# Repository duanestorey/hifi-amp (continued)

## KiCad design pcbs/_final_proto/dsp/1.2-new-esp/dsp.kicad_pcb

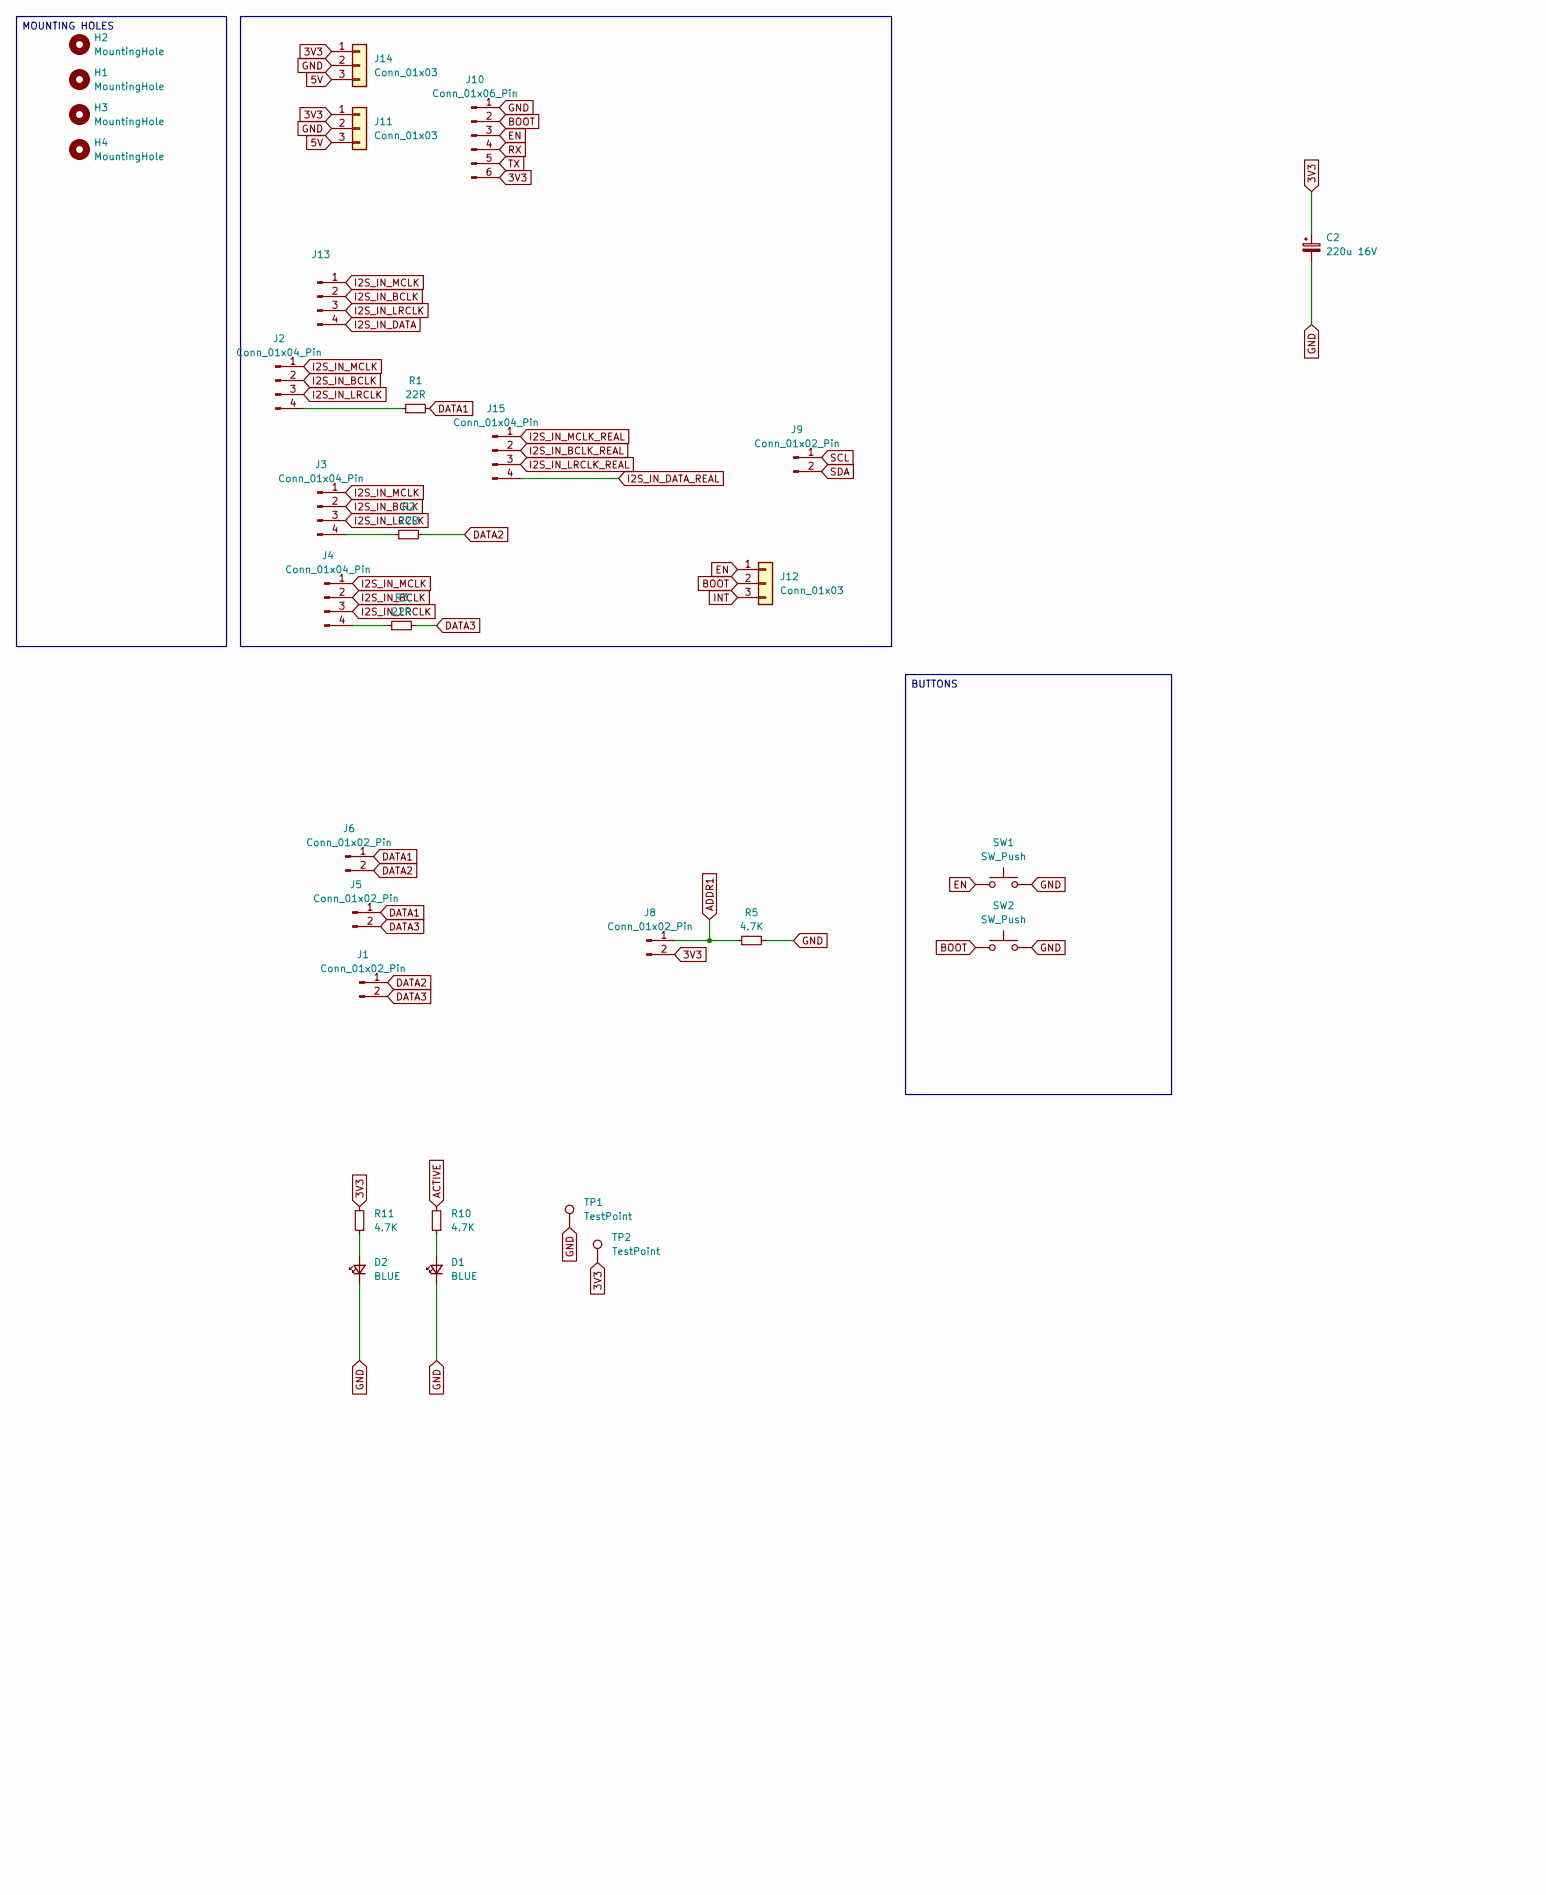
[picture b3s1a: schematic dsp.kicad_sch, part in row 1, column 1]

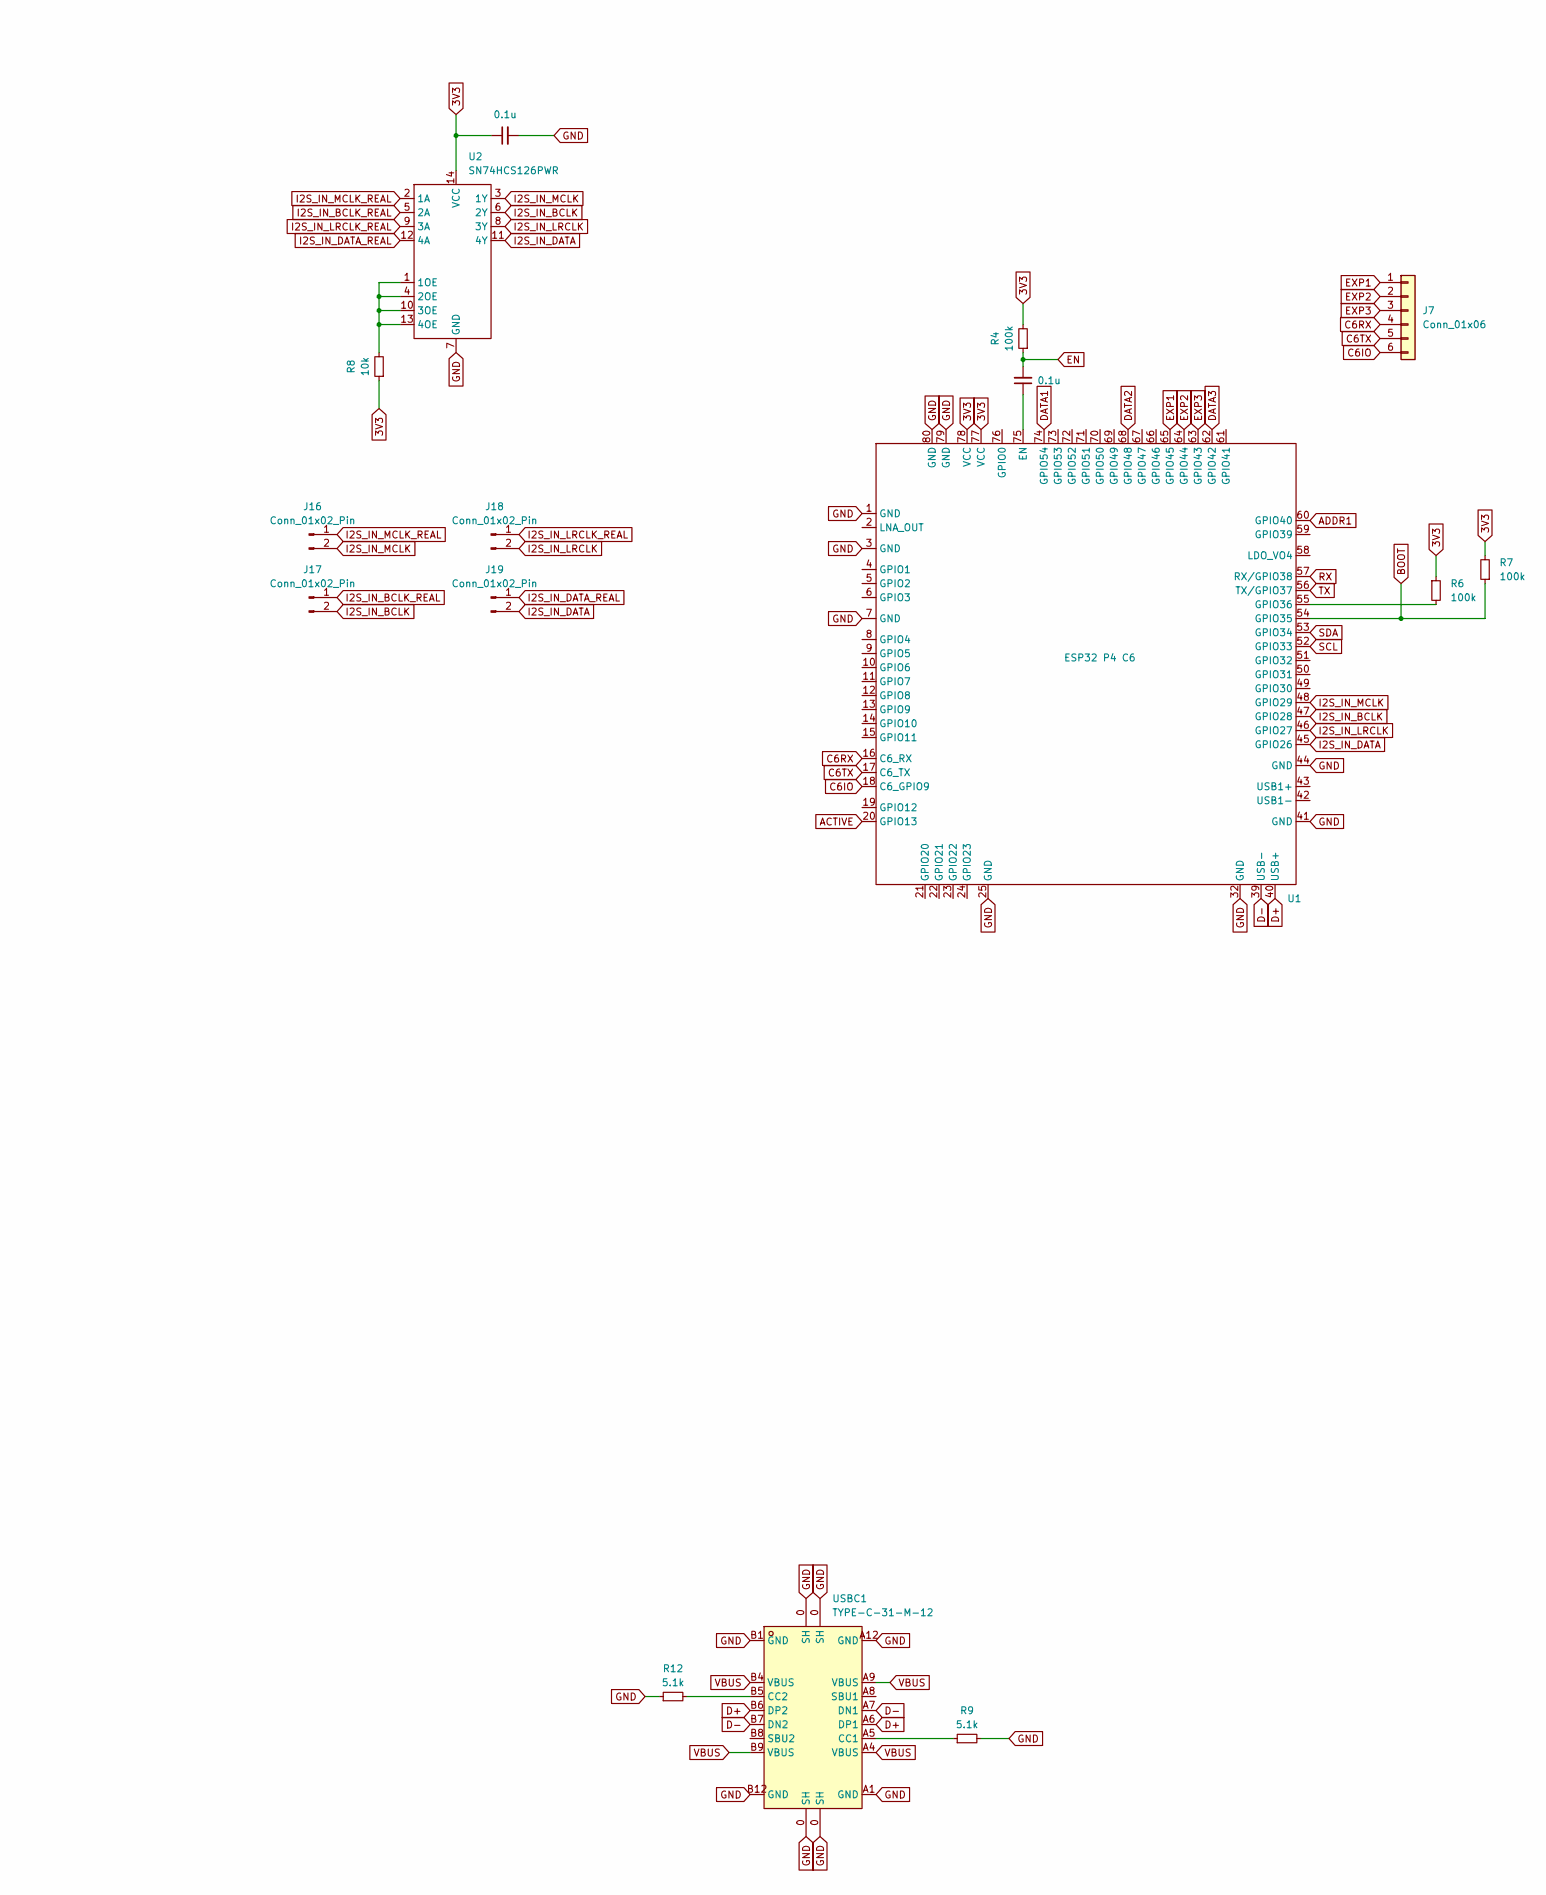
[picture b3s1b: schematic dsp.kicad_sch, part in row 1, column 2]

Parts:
C1, C3: 0.1u; C_0805_2012Metric_Pad1.18x1.45mm_HandSolder
C2: 220u 16V; CP_Elec_6.3x7.7
D1, D2: BLUE; LED_0805_2012Metric_Pad_HandSolder_Duane
H1, H2, H3, H4: MountingHole; MountingHole_3.2mm_M3_DIN965_Pad_TopOnly
J1, J5, J6, J8, J16, J17, J18, J19: Conn_01x02_Pin; PinHeader_1x02_P2.54mm_Vertical
J2, J3, J4, J15: Conn_01x04_Pin; JST_PH_B4B-PH-K_1x04_P2.00mm_Vertical
J7: Conn_01x06; PinHeader_1x06_P2.54mm_Vertical
J9: Conn_01x02_Pin; JST_PH_B2B-PH-K_1x02_P2.00mm_Vertical
J10: Conn_01x06_Pin; PinHeader_1x06_P2.54mm_Vertical
J11, J12, J14: Conn_01x03; JST_PH_B3B-PH-K_1x03_P2.00mm_Vertical
J13: Conn_01x04_Pin; PinHeader_1x04_P2.54mm_Vertical
R1, R2, R3: 22R; R_0805_2012Metric_Pad1.20x1.40mm_HandSolder_Duane; LCSC C23162
R4, R6, R7: 100k; R_0805_2012Metric_Pad1.20x1.40mm_HandSolder_Duane; Mouser 603-RT0805FRE0722RL
R5, R10, R11: 4.7K; R_0805_2012Metric_Pad1.20x1.40mm_HandSolder_Duane; LCSC C23162
R8: 10k; R_0805_2012Metric_Pad1.20x1.40mm_HandSolder_Duane; Mouser 603-RT0805FRE0722RL
R9, R12: 5.1k; R_0805_2012Metric_Pad1.20x1.40mm_HandSolder_Duane; Mouser 603-RT0805FRE0722RL
SW1, SW2: SW_Push; Button Aliexpress 4x4
TP1, TP2: TestPoint; TestPoint_THTPad_1.5x1.5mm_Drill0.7mm
U1: ESP32 P4 C6; ESP32 P4 C6 Module SoC Duane
U2: SN74HCS126PWR; TSSOP-14_4.4x5mm_P0.65mm; Mouser SN74HCS126PWR
USBC1: TYPE-C-31-M-12; USB-C - Duane; LCSC Part C165948

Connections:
3V3: C2.1, C3.1, J8.2, J10.6, J11.1, J14.1, R4.2, R6.1, R7.2, R8.1, R11.2, TP2.1, U1.77 (VCC), U1.78 (VCC), U2.14 (VCC)
5V: J11.3, J14.3
ACTIVE: R10.2, U1.20 (GPIO13)
ADDR1: J8.1, R5.1, U1.60 (GPIO40)
BOOT: J10.2, J12.2, R7.1, SW2.1, U1.54 (GPIO35)
C6IO: J7.6, U1.18 (C6_GPIO9)
C6RX: J7.4, U1.16 (C6_RX)
C6TX: J7.5, U1.17 (C6_TX)
D+: U1.40 (USB+), USBC1.A6 (DP1), USBC1.B6 (DP2)
D-: U1.39 (USB-), USBC1.A7 (DN1), USBC1.B7 (DN2)
DATA1: J5.1, J6.1, R1.2, U1.74 (GPIO54)
DATA2: J1.1, J6.2, R2.2, U1.68 (GPIO48)
DATA3: J1.2, J5.2, R3.2, U1.62 (GPIO42)
EN: C1.2, J10.3, J12.1, R4.1, SW1.1
EXP1: J7.1, U1.65 (GPIO45)
EXP2: J7.2, U1.64 (GPIO44)
EXP3: J7.3, U1.63 (GPIO43)
GND: C2.2, C3.2, D1.1 (K), D2.1 (K), J10.1, J11.2, J14.2, R5.2, R9.2, R12.1, SW1.2, SW2.2, TP1.1, U1.1 (GND), U1.3 (GND), U1.7 (GND), U1.25 (GND), U1.32 (GND), U1.41 (GND), U1.44 (GND), U1.79 (GND), U1.80 (GND), U2.7 (GND), USBC1.0 (SH), USBC1.A1 (GND), USBC1.A12 (GND), USBC1.B1 (GND), USBC1.B12 (GND)
I2S_IN_BCLK: J2.2, J3.2, J4.2, J13.2, J17.2, U1.47 (GPIO28), U2.6 (2Y)
I2S_IN_BCLK_REAL: J15.2, J17.1, U2.5 (2A)
I2S_IN_DATA: J13.4, J19.2, U1.45 (GPIO26), U2.11 (4Y)
I2S_IN_DATA_REAL: J15.4, J19.1, U2.12 (4A)
I2S_IN_LRCLK: J2.3, J3.3, J4.3, J13.3, J18.2, U1.46 (GPIO27), U2.8 (3Y)
I2S_IN_LRCLK_REAL: J15.3, J18.1, U2.9 (3A)
I2S_IN_MCLK: J2.1, J3.1, J4.1, J13.1, J16.2, U1.48 (GPIO29), U2.3 (1Y)
I2S_IN_MCLK_REAL: J15.1, J16.1, U2.2 (1A)
INT: J12.3
unnamed: D1.2 (A), R10.1
unnamed: D2.2 (A), R11.1
unnamed: J2.4, R1.1
unnamed: J3.4, R2.1
unnamed: J4.4, R3.1
unnamed: C1.1, U1.75 (EN)
unnamed: R6.2, U1.55 (GPIO36)
unnamed: R8.2, U2.1 (1OE), U2.4 (2OE), U2.10 (3OE), U2.13 (4OE)
unnamed: R9.1, USBC1.A5 (CC1)
unnamed: R12.2, USBC1.B5 (CC2)
RX: J10.4, U1.57 (RX/GPIO38)
SCL: J9.1, U1.52 (GPIO33)
SDA: J9.2, U1.53 (GPIO34)
TX: J10.5, U1.56 (TX/GPIO37)
VBUS: USBC1.A4 (VBUS), USBC1.A9 (VBUS), USBC1.B4 (VBUS), USBC1.B9 (VBUS)

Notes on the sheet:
MOUNTING HOLES
BUTTONS

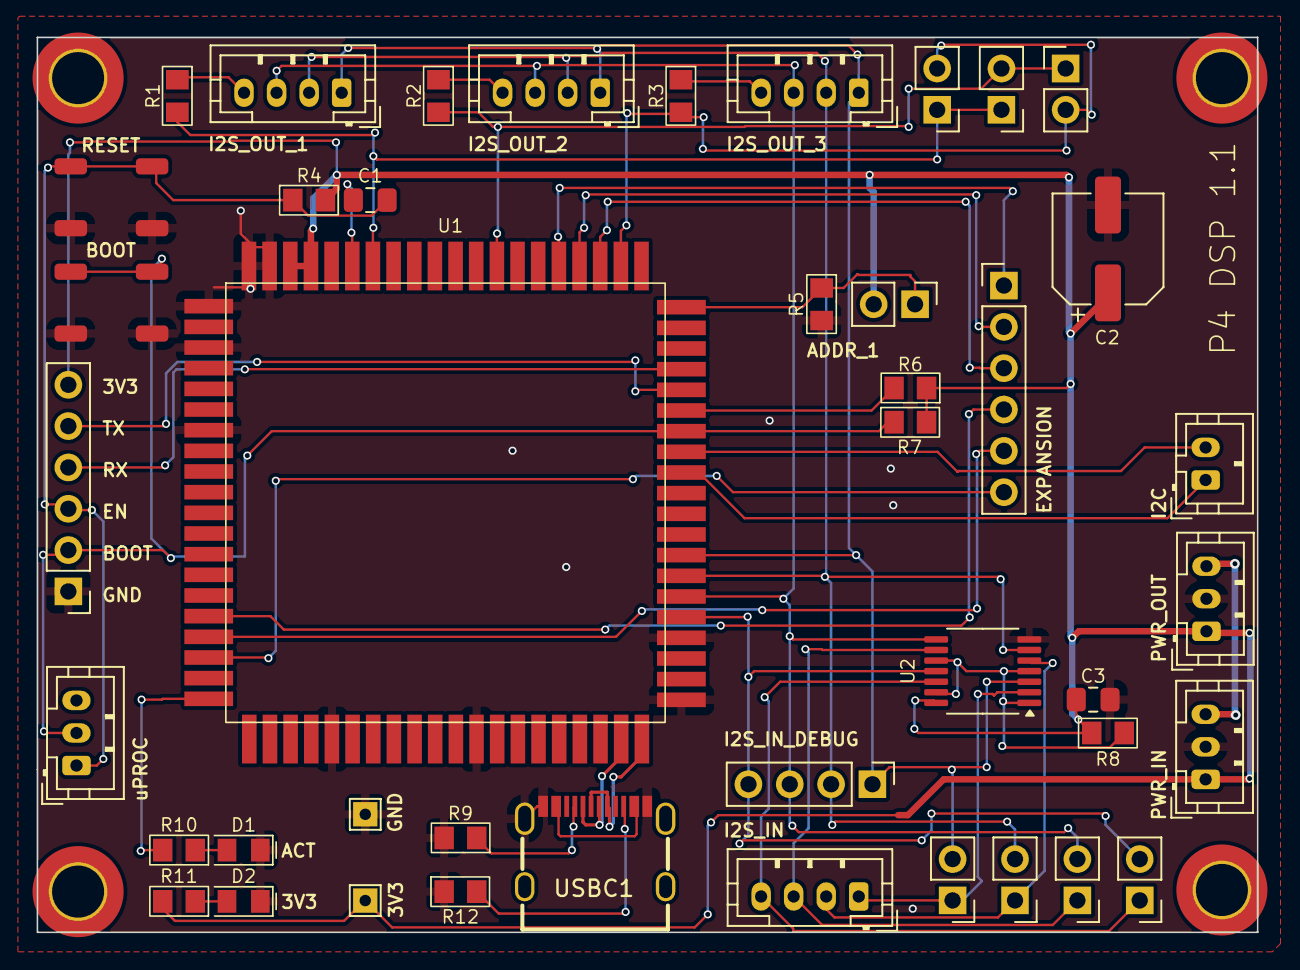
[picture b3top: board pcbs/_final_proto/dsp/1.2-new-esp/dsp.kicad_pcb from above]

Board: 2 copper layers, 75.0 x 55.0 mm, 47 parts (0 on the bottom side), 41 nets.

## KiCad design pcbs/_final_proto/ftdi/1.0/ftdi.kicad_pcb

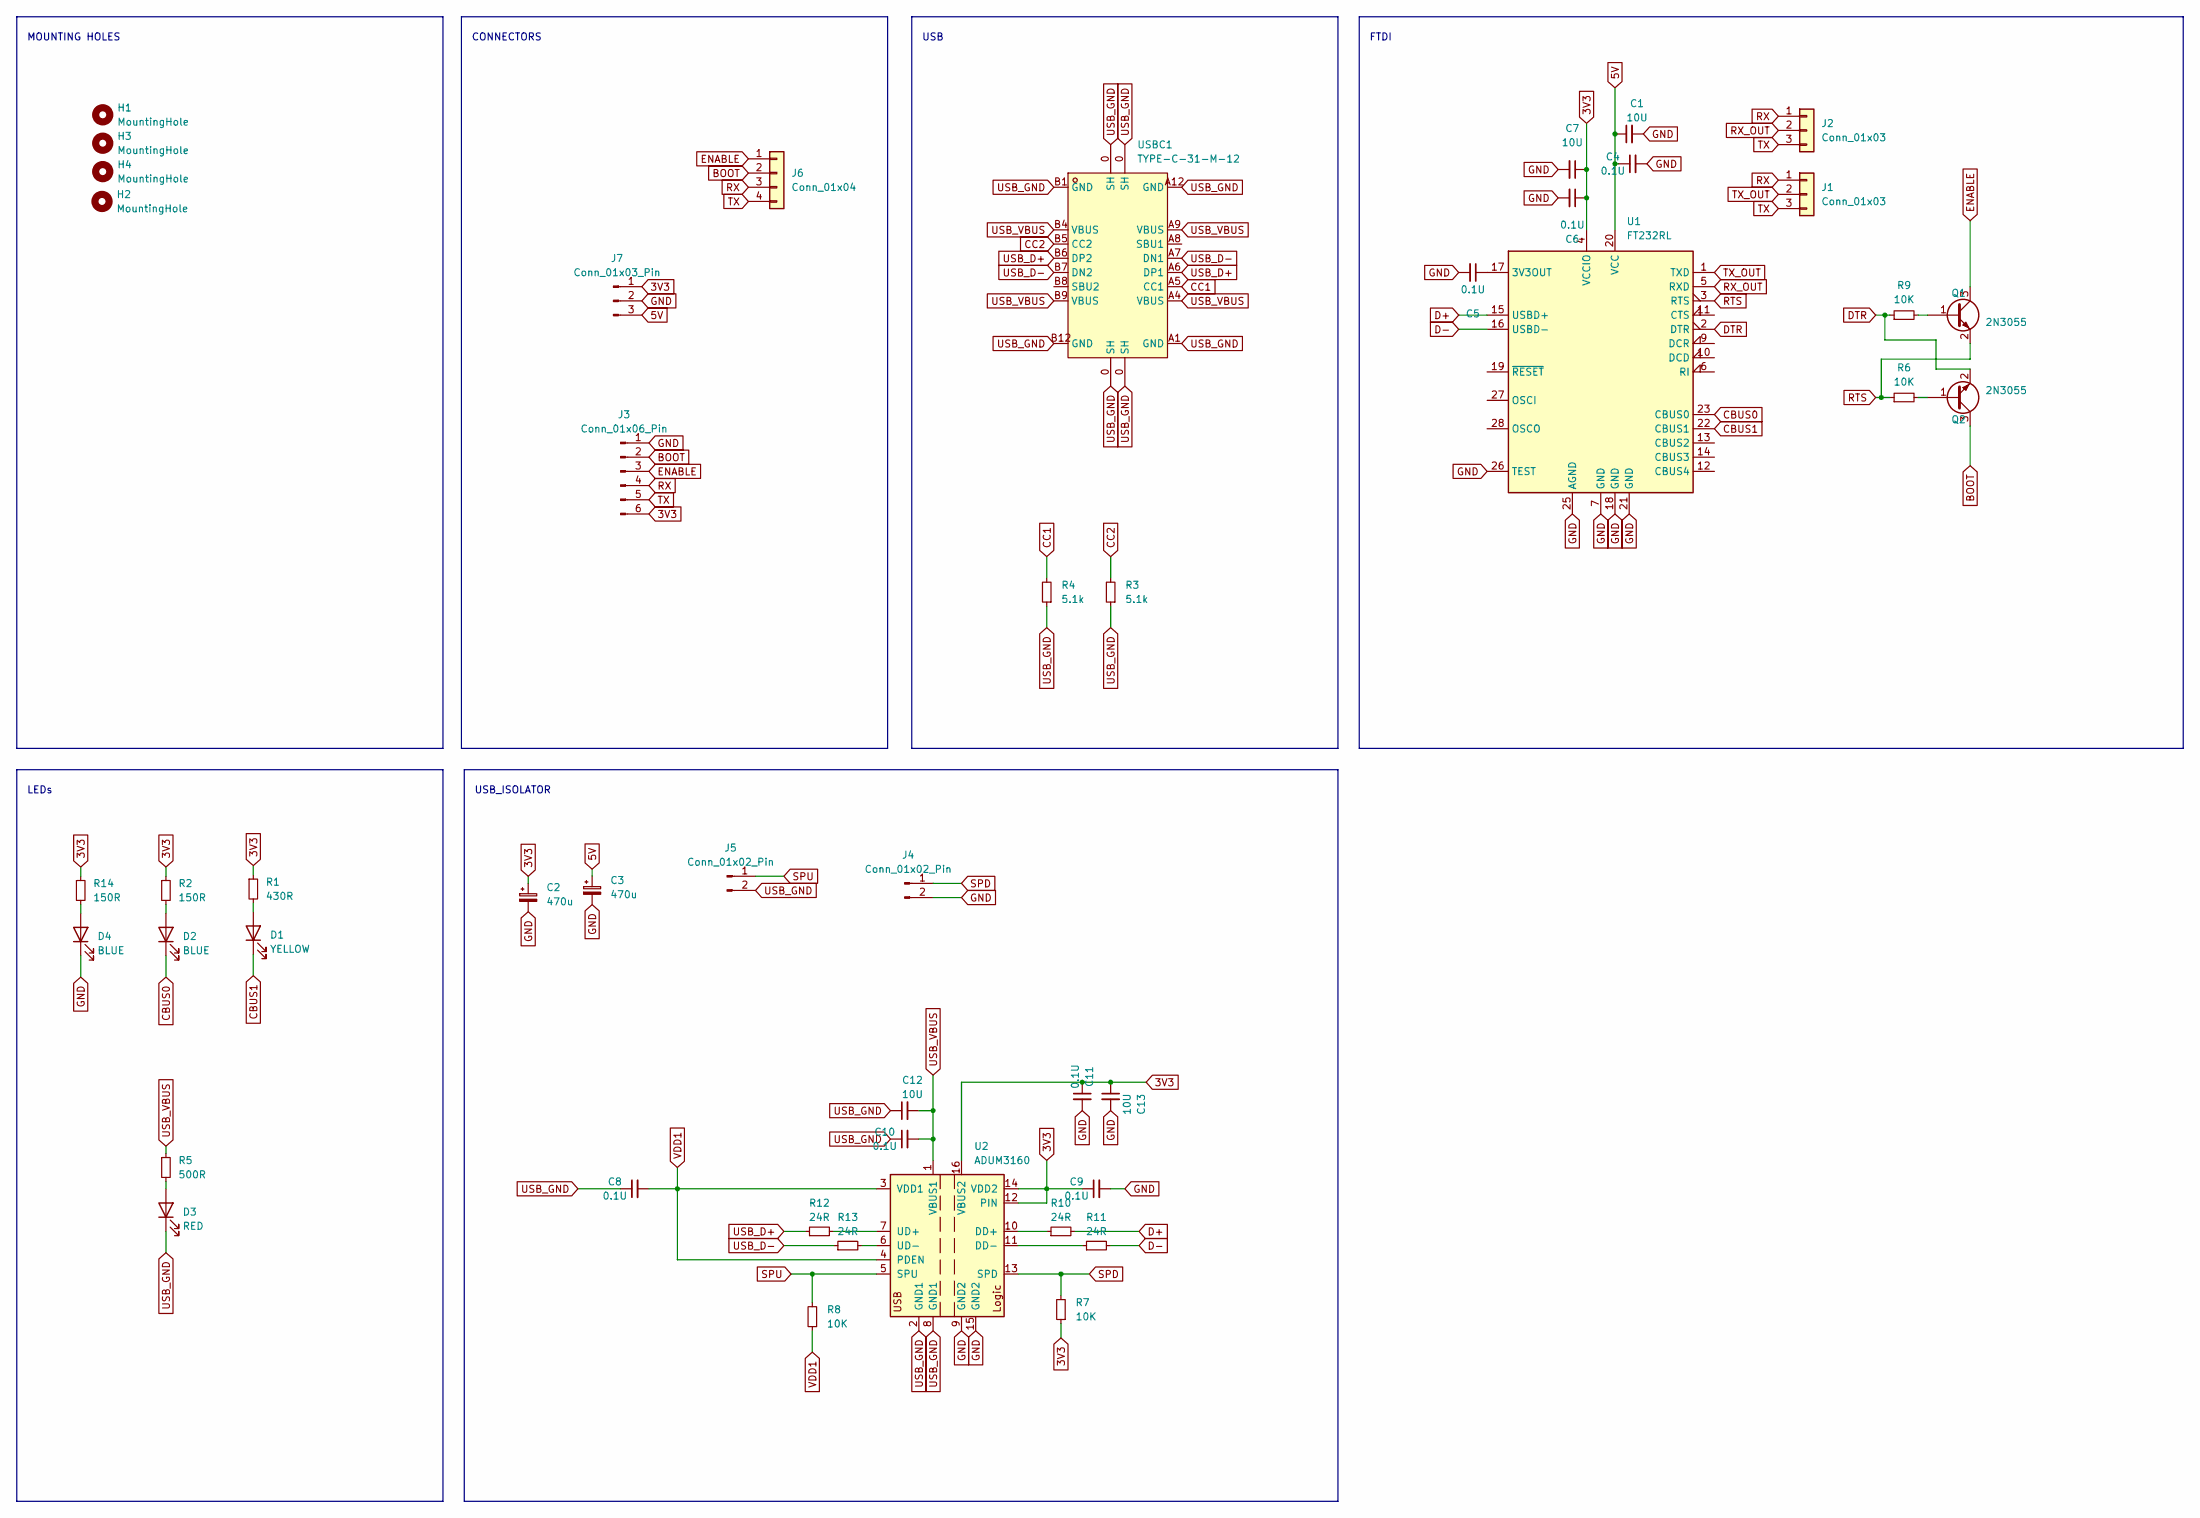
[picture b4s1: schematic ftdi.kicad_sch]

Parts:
C1, C7, C12, C13: 10U; C_1206_3216Metric_Pad1.33x1.80mm_HandSolder
C2, C3: 470u; CP_Radial_D6.3mm_P2.50mm
C4, C5, C6, C8, C9, C10, C11: 0.1U; C_0805_2012Metric_Pad1.18x1.45mm_HandSolder
D1: YELLOW; LED_0603_1608Metric_Pad1.05x0.95mm_HandSolder; LCSC XL-1608UBC-04
D2, D4: BLUE; LED_0603_1608Metric_Pad1.05x0.95mm_HandSolder; LCSC XL-1608UBC-04
D3: RED; LED_0603_1608Metric_Pad1.05x0.95mm_HandSolder; LCSC XL-1608UBC-04
H1, H2, H3, H4: MountingHole; MountingHole_3.2mm_M3_DIN965_Pad_TopOnly
J1, J2: Conn_01x03; PinHeader_1x03_P2.54mm_Vertical
J3: Conn_01x06_Pin; PinHeader_1x06_P2.54mm_Vertical
J4, J5: Conn_01x02_Pin; PinHeader_1x02_P2.54mm_Vertical
J6: Conn_01x04; JST_PH_B4B-PH-K_1x04_P2.00mm_Vertical
J7: Conn_01x03_Pin; JST_PH_B3B-PH-K_1x03_P2.00mm_Vertical
Q1, Q2: 2N3055; TSOT-23
R1: 430R; R_0603_1608Metric_Pad0.98x0.95mm_HandSolder
R2, R14: 150R; R_0603_1608Metric_Pad0.98x0.95mm_HandSolder
R3, R4: 5.1k; R_0805_2012Metric_Pad1.20x1.40mm_HandSolder
R5: 500R; R_0603_1608Metric_Pad0.98x0.95mm_HandSolder
R6, R7, R8, R9: 10K; R_0603_1608Metric_Pad0.98x0.95mm_HandSolder
R10, R11, R12, R13: 24R; R_0603_1608Metric_Pad0.98x0.95mm_HandSolder
U1: FT232RL; SSOP-28_5.3x10.2mm_P0.65mm
U2: ADUM3160; SOIC-16W_7.5x10.3mm_P1.27mm; Mouser 584-ADUM3160BRWZ-R
USBC1: TYPE-C-31-M-12; USB-C_SMD-TYPE-C-31-M-12; LCSC Part C165948

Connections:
3V3: C2.1, C6.1, C7.1, C9.1, C11.1, C13.1, J3.6, J7.1, R1.1, R2.1, R7.1, R14.1, U1.4 (VCCIO), U2.12 (PIN), U2.14 (VDD2), U2.16 (VBUS2)
5V: C1.1, C3.1, C4.1, J7.3, U1.20 (VCC)
BOOT: J3.2, J6.2, Q2.3 (C)
CBUS0: D2.1 (K), U1.23 (CBUS0)
CBUS1: D1.1 (K), U1.22 (CBUS1)
CC1: R4.2, USBC1.A5 (CC1)
CC2: R3.2, USBC1.B5 (CC2)
D+: R10.2, U1.15 (USBD+)
D-: R11.2, U1.16 (USBD-)
DTR: Q2.2 (E), R9.1, U1.2 (DTR)
ENABLE: J3.3, J6.1, Q1.3 (C)
GND: C1.2, C2.2, C3.2, C4.2, C5.2, C6.2, C7.2, C9.2, C11.2, C13.2, D4.1 (K), J3.1, J4.2, J7.2, U1.7 (GND), U1.18 (GND), U1.21 (GND), U1.25 (AGND), U1.26 (TEST), U2.9 (GND2), U2.15 (GND2)
unnamed: D1.2 (A), R1.2
unnamed: D2.2 (A), R2.2
unnamed: D3.2 (A), R5.2
unnamed: D4.2 (A), R14.2
unnamed: Q1.1 (B), R9.2
unnamed: Q2.1 (B), R6.2
unnamed: C5.1, U1.17 (3V3OUT)
unnamed: R10.1, U2.10 (DD+)
unnamed: R11.1, U2.11 (DD-)
unnamed: R12.2, U2.7 (UD+)
unnamed: R13.2, U2.6 (UD-)
RTS: Q1.2 (E), R6.1, U1.3 (RTS)
RX: J1.1, J2.1, J3.4, J6.3
RX_OUT: J2.2, U1.5 (RXD)
SPD: J4.1, R7.2, U2.13 (SPD)
SPU: J5.1, R8.2, U2.5 (SPU)
TX: J1.3, J2.3, J3.5, J6.4
TX_OUT: J1.2, U1.1 (TXD)
USB_D+: R12.1, USBC1.A6 (DP1), USBC1.B6 (DP2)
USB_D-: R13.1, USBC1.A7 (DN1), USBC1.B7 (DN2)
USB_GND: C8.1, C10.1, C12.1, D3.1 (K), J5.2, R3.1, R4.1, U2.2 (GND1), U2.8 (GND1), USBC1.0 (SH), USBC1.A1 (GND), USBC1.A12 (GND), USBC1.B1 (GND), USBC1.B12 (GND)
USB_VBUS: C10.2, C12.2, R5.1, U2.1 (VBUS1), USBC1.A4 (VBUS), USBC1.A9 (VBUS), USBC1.B4 (VBUS), USBC1.B9 (VBUS)
VDD1: C8.2, R8.1, U2.3 (VDD1), U2.4 (PDEN)

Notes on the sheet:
FTDI
LEDs
CONNECTORS
USB_ISOLATOR
USB
MOUNTING HOLES

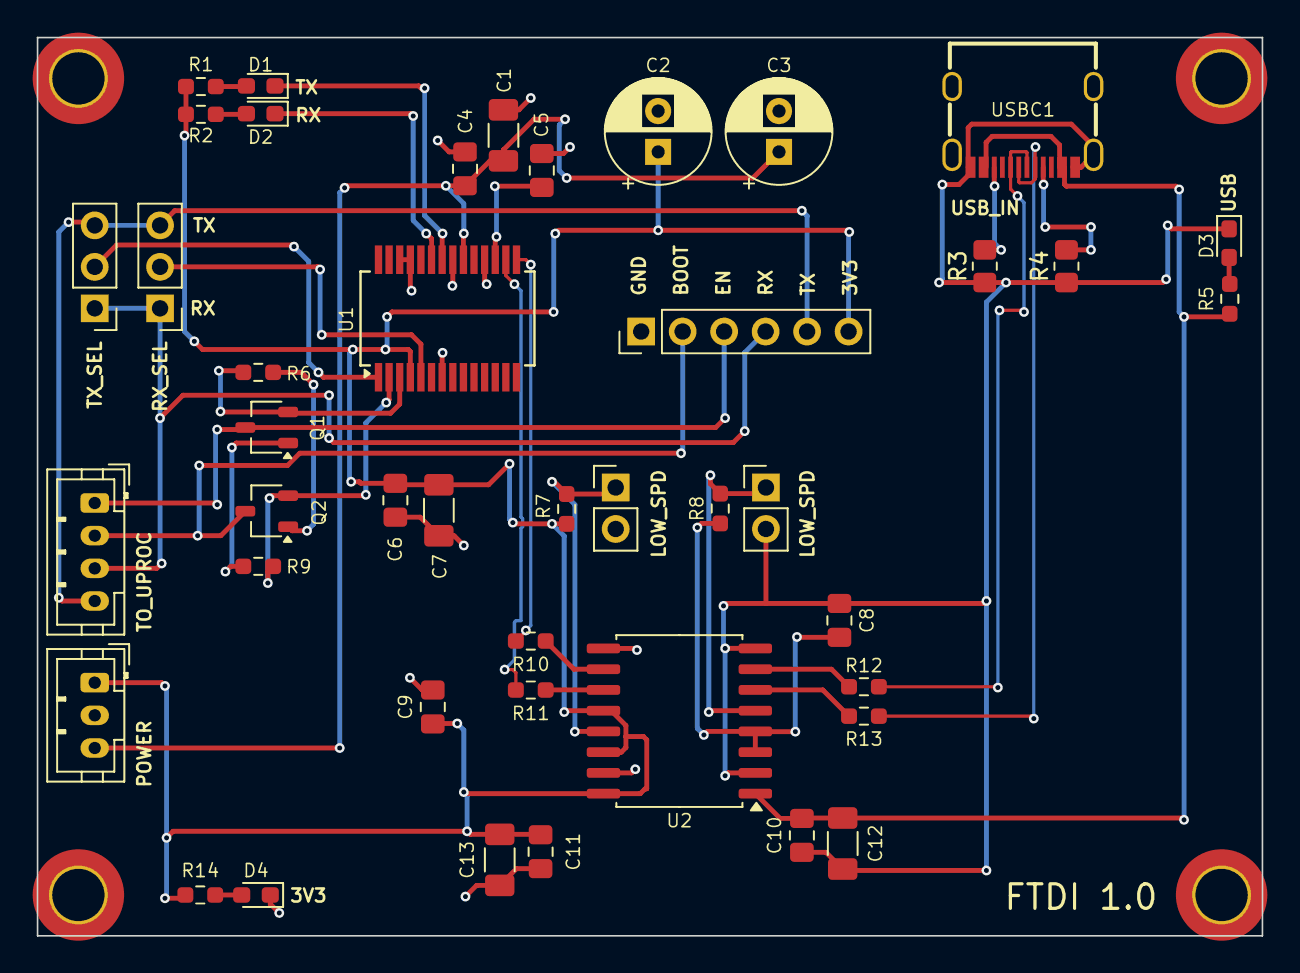
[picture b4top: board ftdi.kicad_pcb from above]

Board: 2 copper layers, 75.0 x 55.0 mm, 47 parts (0 on the bottom side), 35 nets.

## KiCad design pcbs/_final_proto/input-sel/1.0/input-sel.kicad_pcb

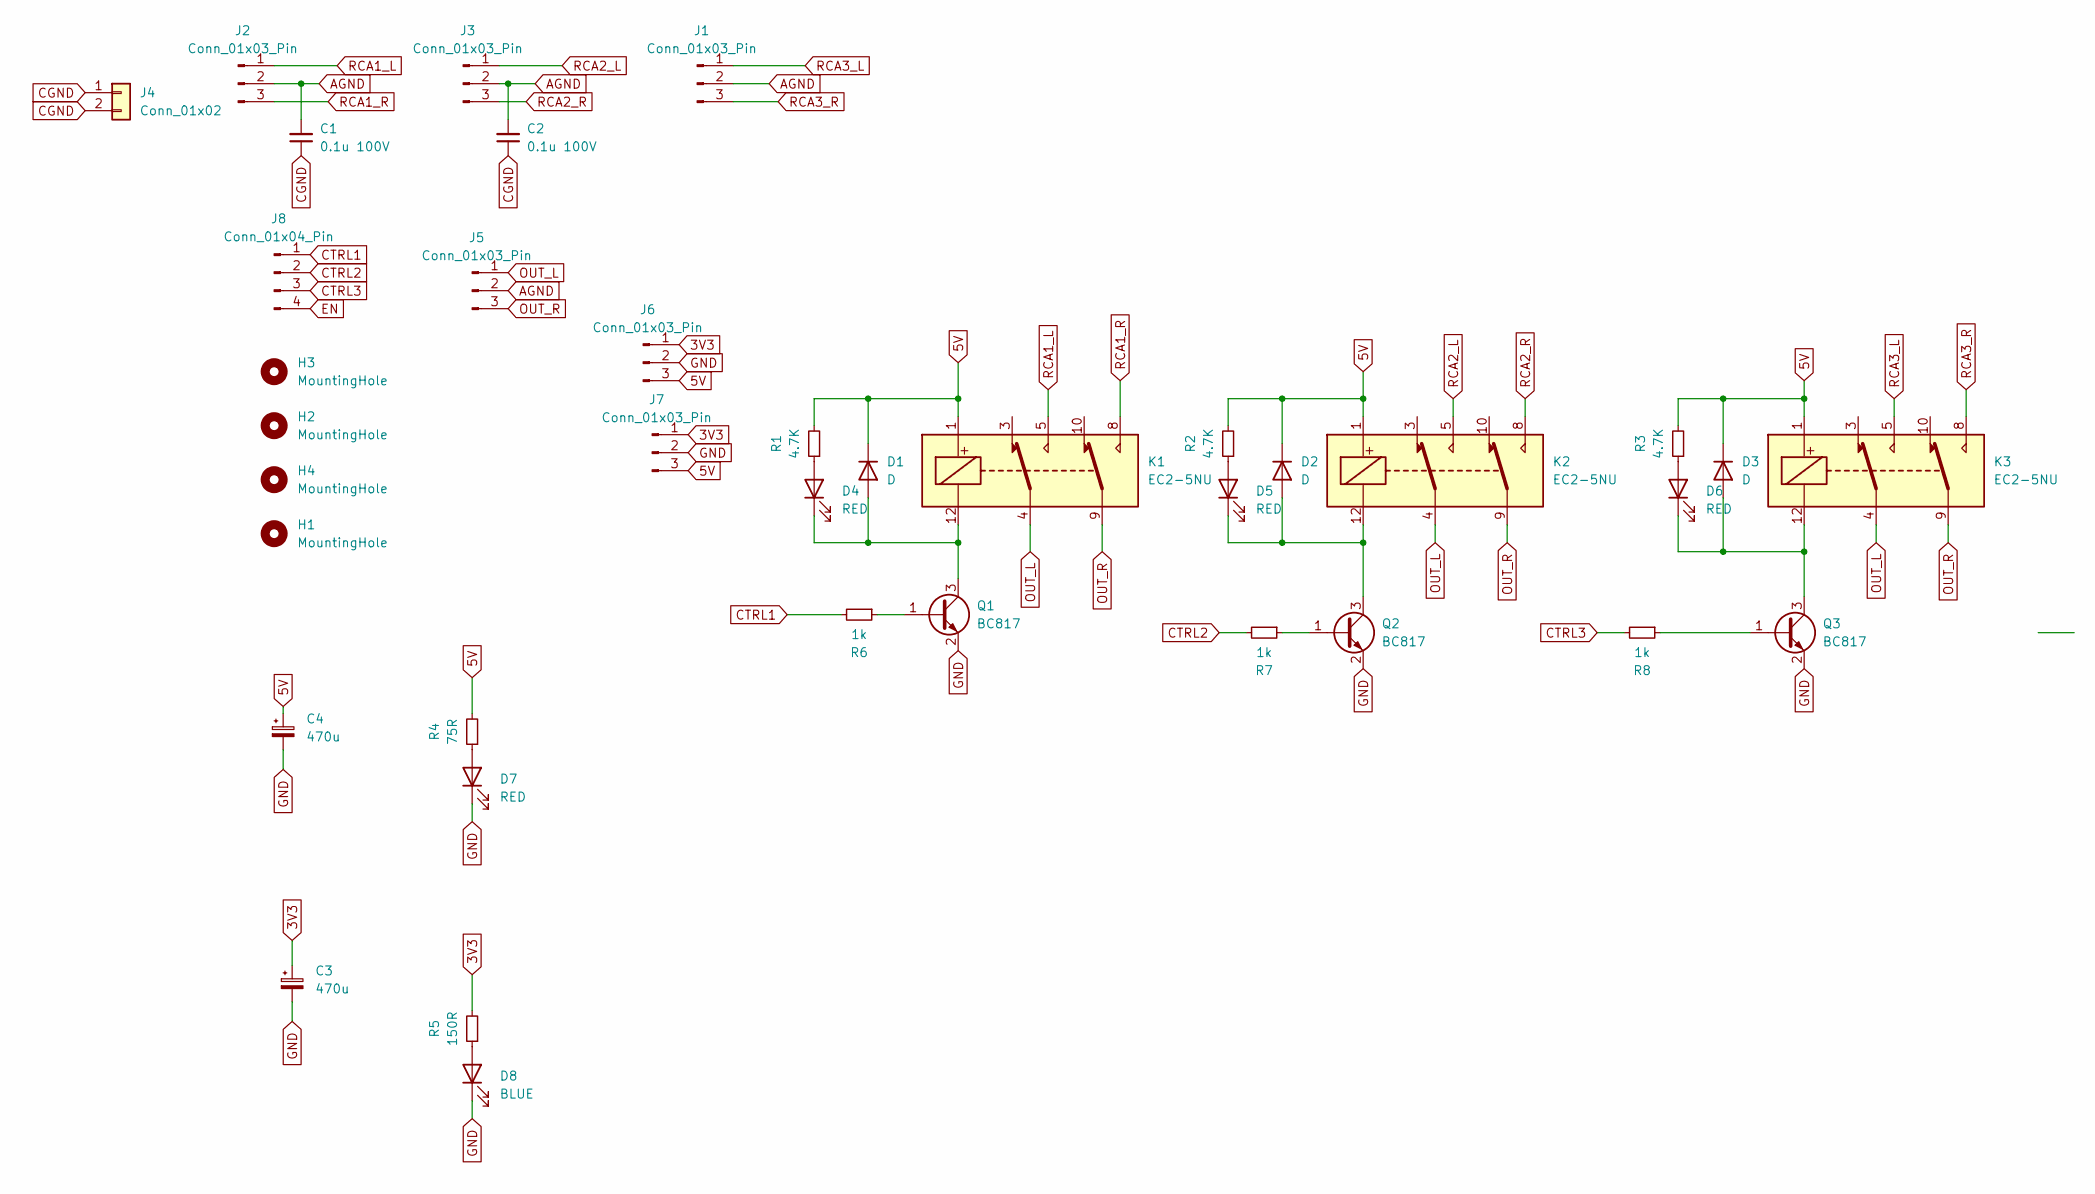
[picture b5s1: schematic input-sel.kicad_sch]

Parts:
C1, C2: 0.1u 100V; C_1206_3216Metric; Mouser 791-1206B104K101CT
C3, C4: 470u; CP_Radial_D6.3mm_P2.50mm
D1, D2, D3: D; D_SMA; Mouser 863-NRVA4005T3G
D4, D5, D6, D7: RED; LED_0805_2012Metric_Pad1.15x1.40mm_HandSolder
D8: BLUE; LED_0805_2012Metric_Pad1.15x1.40mm_HandSolder
H1, H2, H3, H4: MountingHole; MountingHole_3.2mm_M3_DIN965_Pad_TopOnly
J1, J5, J6, J7: Conn_01x03_Pin; JST_PH_B3B-PH-K_1x03_P2.00mm_Vertical
J2, J3: Conn_01x03_Pin; TerminalBlock_Phoenix_PT-1,5-3-3.5-H_1x03_P3.50mm_Horizontal
J4: Conn_01x02; TerminalBlock_Phoenix_PT-1,5-2-3.5-H_1x02_P3.50mm_Horizontal
J8: Conn_01x04_Pin; JST_PH_B4B-PH-K_1x04_P2.00mm_Vertical
K1, K2, K3: EC2-5NU; KEMET EA2; Mouser 80-EA2-12NU
Q1, Q2, Q3: BC817; SOT-23
R1, R2, R3: 4.7K; R_0805_2012Metric_Pad1.20x1.40mm_HandSolder
R4: 75R; R_0805_2012Metric_Pad1.20x1.40mm_HandSolder
R5: 150R; R_0805_2012Metric_Pad1.20x1.40mm_HandSolder
R6, R7, R8: 1k; R_0805_2012Metric_Pad1.20x1.40mm_HandSolder; Mouser 603-AC0603JR-07820RL

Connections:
3V3: C3.1, J6.1, J7.1, R5.2
5V: C4.1, D1.1 (K), D2.1 (K), D3.1 (K), J6.3, J7.3, K1.1, K2.1, K3.1, R1.2, R2.2, R3.2, R4.2
AGND: C1.2, C2.2, J1.2, J2.2, J3.2, J5.2
CGND: C1.1, C2.1, J4.1, J4.2
CTRL1: J8.1, R6.2
CTRL2: J8.2, R7.2
CTRL3: J8.3, R8.2
EN: J8.4
GND: C3.2, C4.2, D7.1 (K), D8.1 (K), J6.2, J7.2, Q1.2 (E), Q2.2 (E), Q3.2 (E)
unnamed: D1.2 (A), D4.1 (K), K1.12, Q1.3 (C)
unnamed: D2.2 (A), D5.1 (K), K2.12, Q2.3 (C)
unnamed: D3.2 (A), D6.1 (K), K3.12, Q3.3 (C)
unnamed: D4.2 (A), R1.1
unnamed: D5.2 (A), R2.1
unnamed: D6.2 (A), R3.1
unnamed: D7.2 (A), R4.1
unnamed: D8.2 (A), R5.1
unnamed: Q1.1 (B), R6.1
unnamed: Q2.1 (B), R7.1
unnamed: Q3.1 (B), R8.1
OUT_L: J5.1, K1.4, K2.4, K3.4
OUT_R: J5.3, K1.9, K2.9, K3.9
RCA1_L: J2.1, K1.5
RCA1_R: J2.3, K1.8
RCA2_L: J3.1, K2.5
RCA2_R: J3.3, K2.8
RCA3_L: J1.1, K3.5
RCA3_R: J1.3, K3.8

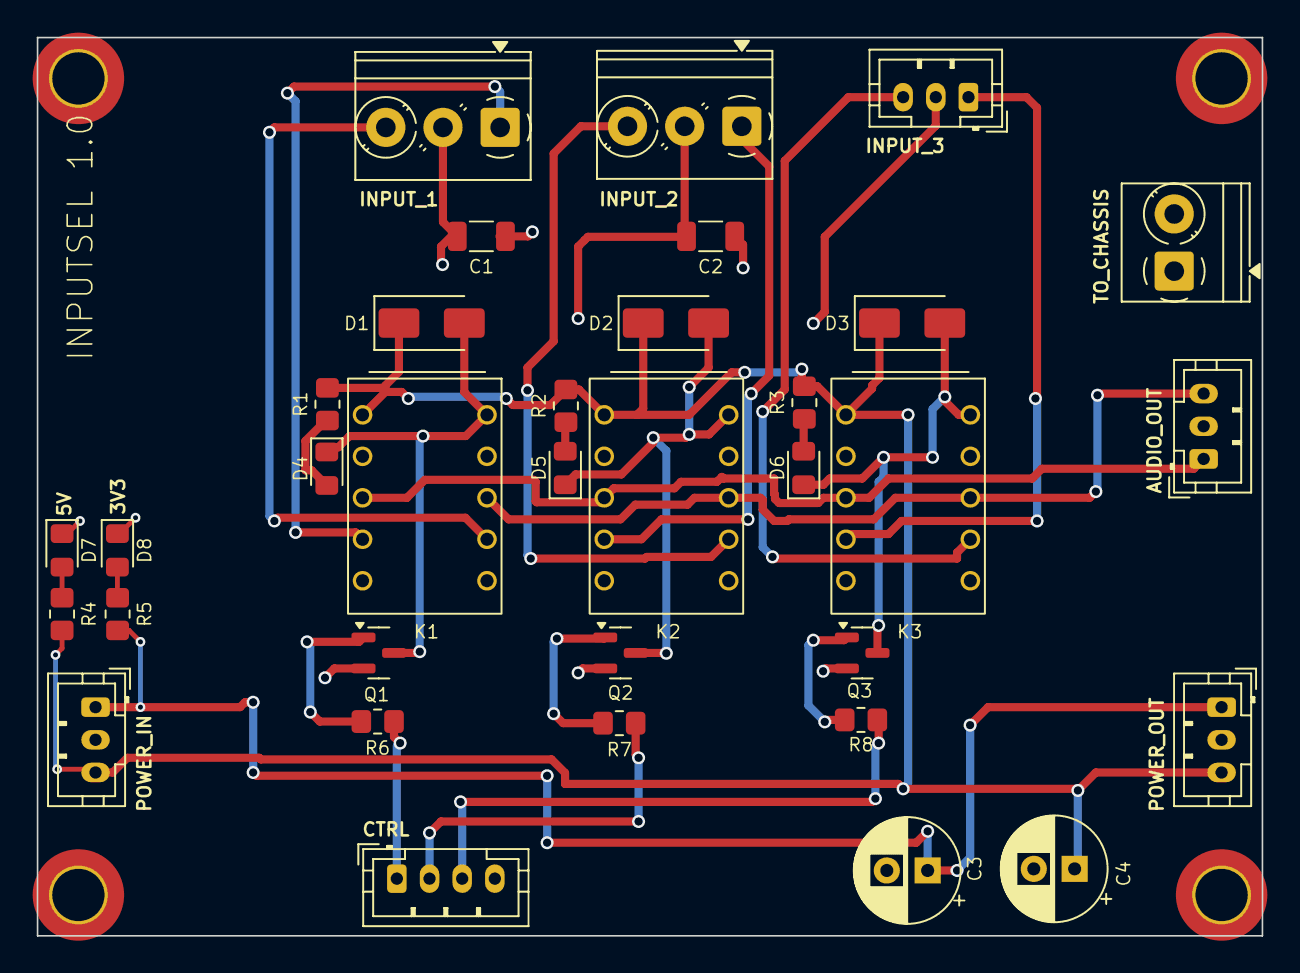
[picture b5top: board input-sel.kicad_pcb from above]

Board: 2 copper layers, 75.0 x 55.0 mm, 38 parts (0 on the bottom side), 27 nets.

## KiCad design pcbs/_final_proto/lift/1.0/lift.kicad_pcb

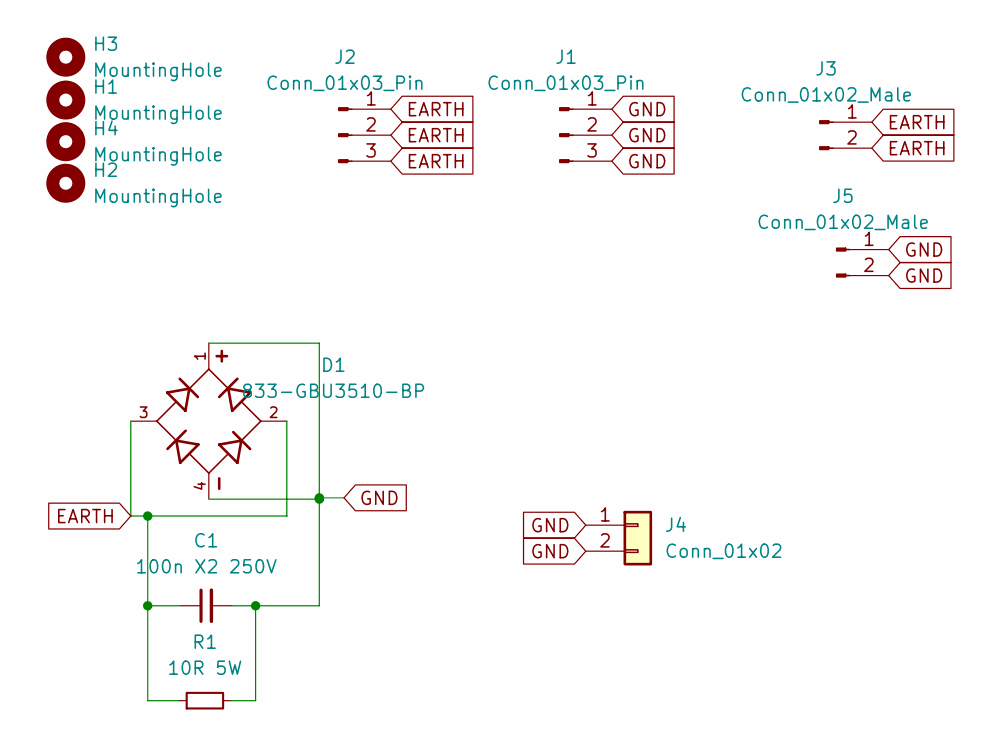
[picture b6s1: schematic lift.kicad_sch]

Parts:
C1: 100n X2 250V; C_Rect_L18.0mm_W5.0mm_P15.00mm_FKS3_FKP3; Mouser 871-B32922X2104K000
D1: 833-GBU3510-BP; Diode_Bridge_Vishay_GBU; Mouser 833-GBU3510-BP
H1, H2, H3, H4: MountingHole; MountingHole_3.2mm_M3_DIN965_Pad_TopOnly
J1, J2: Conn_01x03_Pin; TerminalBlock_Phoenix_PT-1,5-3-5.0-H_1x03_P5.00mm_Horizontal
J3: Conn_01x02_Male; TerminalBlock_Phoenix_PT-1,5-2-5.0-H_1x02_P5.00mm_Horizontal
J4: Conn_01x02; TerminalBlock_Phoenix_PT-1,5-2-5.0-H_1x02_P5.00mm_Horizontal
J5: Conn_01x02_Male; JST_VH_B2P-VH-B_1x02_P3.96mm_Vertical
R1: 10R 5W; R_Axial_DIN0617_L17.0mm_D6.0mm_P25.40mm_Horizontal; Mouser 594-AC05W10R00J

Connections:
EARTH: C1.1, D1.2, D1.3, J2.1, J2.2, J2.3, J3.1, J3.2, R1.1
GND: C1.2, D1.1, D1.4, J1.1, J1.2, J1.3, J4.1, J4.2, J5.1, J5.2, R1.2

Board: 2 copper layers, 12 parts (0 on the bottom side), 2 nets, no tracks yet.
